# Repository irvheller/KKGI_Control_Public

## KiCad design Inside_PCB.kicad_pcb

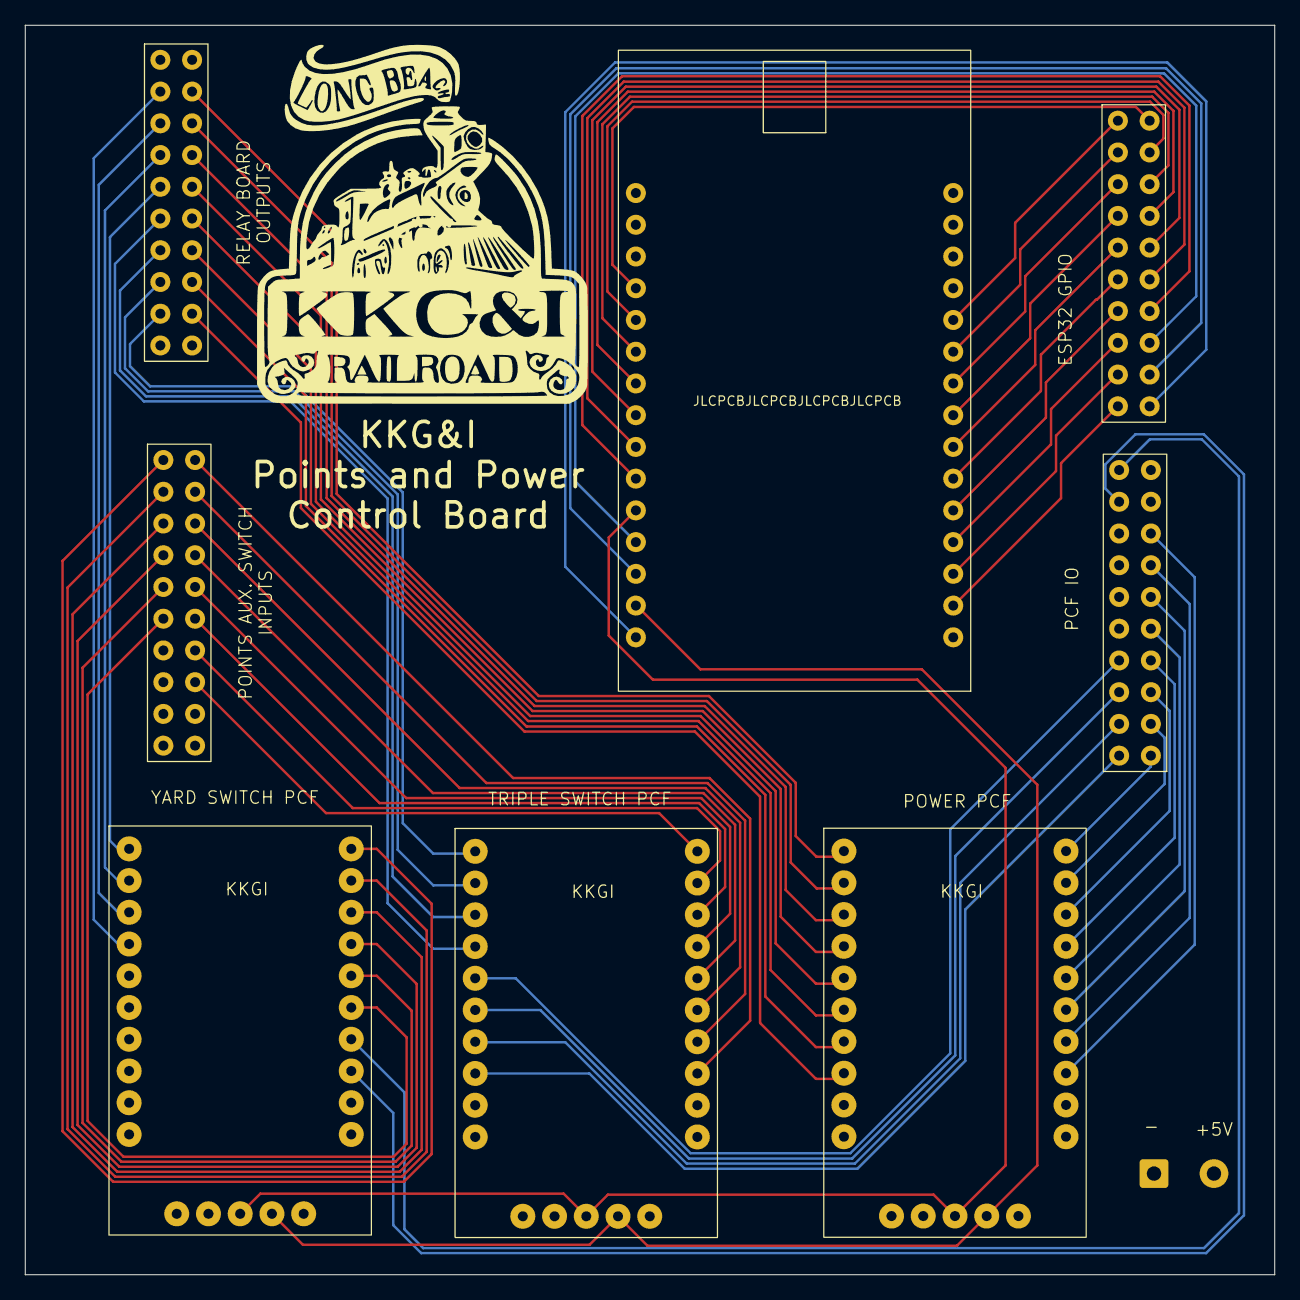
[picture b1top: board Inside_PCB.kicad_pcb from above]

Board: 4 copper layers, 100.0 x 100.0 mm, 9 parts (0 on the bottom side), 72 nets.

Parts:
J1: Screw_Terminal_01x02; SolderWire-0.5sqmm_1x02_P4.8mm_D0.9mm_OD2.3mm
U1: ESP32_DEVKIT
U2: Power PCF; PCF8575
U3: Yard Switch PCF; PCF8575
U4: Triple Switch PCF; PCF8575
U5: Points Aux Switches; 2X10_HEADER
U6: Relay Board; 2X10_HEADER
U7, U8: 2X10_HEADER

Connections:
+5V: J1.2, U1.30 (VIN), U2.2 (VD0), U2.19 (VD0), U2.22 (VCC), U3.2 (VD0), U3.19 (VD0), U3.22 (VCC), U4.2 (VD0), U4.19 (VD0), U4.22 (VCC), U6.1, U6.20
GND: J1.1, U1.2 (GND), U1.29 (GND), U2.1 (GND), U2.20 (GND), U2.21 (GND), U3.1 (GND), U3.20 (GND), U3.21 (GND), U4.1 (GND), U4.20 (GND), U4.21 (GND), U6.10, U6.11
unnamed: U1.13 (GPIO1), U8.2
unnamed: U1.4 (GPIO2), U8.10
unnamed: U1.12 (GPIO3), U8.3
unnamed: U1.5 (GPIO4), U8.9
unnamed: U1.8 (GPIO5), U8.6
unnamed: U1.26 (GPIO14), U8.11
unnamed: U1.6 (GPIO16), U8.8
unnamed: U1.7 (GPIO17), U8.7
unnamed: U1.9 (GPIO18), U8.5
unnamed: U1.10 (GPIO19), U8.4
unnamed: U1.15 (GPIO23), U8.1
unnamed: U1.23 (GPIO25), U8.14
unnamed: U1.24 (GPIO26), U8.13
unnamed: U1.25 (GPIO27), U8.12
unnamed: U1.21 (GPIO32), U8.16
unnamed: U1.22 (GPIO33), U8.15
unnamed: U1.19 (GPIO34), U8.18
unnamed: U1.20 (GPIO35), U8.17
unnamed: U1.17 (GPIO36), U8.20
unnamed: U1.18 (GPIO39), U8.19
unnamed: U1.14 (I2C_SCL), U2.24 (SCL), U3.24 (SCL), U4.24 (SCL)
unnamed: U1.11 (I2C_SDA), U2.23 (SDA), U3.23 (SDA), U4.23 (SDA)
unnamed: U2.3 (P00), U7.18
unnamed: U2.4 (P01), U7.17
unnamed: U2.5 (P02), U7.16
unnamed: U2.6 (P03), U7.15
unnamed: U2.7 (P04), U7.14
unnamed: U2.8 (P05), U7.13
unnamed: U2.9 (P06), U7.12
unnamed: U2.10 (P07), U7.11
unnamed: U2.11 (P10), U6.9
unnamed: U2.12 (P11), U6.8
unnamed: U2.13 (P12), U6.7
unnamed: U2.14 (P13), U6.6
unnamed: U2.15 (P14), U6.5
unnamed: U2.16 (P15), U6.4
unnamed: U2.17 (P16), U6.3
unnamed: U2.18 (P17), U6.2
unnamed: U3.3 (P00), U7.2
unnamed: U3.4 (P01), U7.1
unnamed: U3.5 (P02), U5.16
unnamed: U3.6 (P03), U5.15
unnamed: U3.7 (P04), U5.14
unnamed: U3.8 (P05), U5.13
unnamed: U3.9 (P06), U5.12
unnamed: U3.10 (P07), U5.11
unnamed: U3.11 (P10), U6.15
unnamed: U3.12 (P11), U6.14
unnamed: U3.13 (P12), U6.13
unnamed: U3.14 (P13), U6.12
unnamed: U3.15 (P14), U7.3
unnamed: U3.16 (P15), U7.4
unnamed: U3.17 (P16), U7.5
unnamed: U3.18 (P17), U7.6
unnamed: U4.3 (P00), U5.10
unnamed: U4.4 (P01), U5.9
unnamed: U4.5 (P02), U5.8
unnamed: U4.6 (P03), U5.7
unnamed: U4.7 (P04), U5.6
unnamed: U4.8 (P05), U5.5
unnamed: U4.9 (P06), U5.4
unnamed: U4.10 (P07), U5.3
unnamed: U4.11 (P10), U6.19
unnamed: U4.12 (P11), U6.18
unnamed: U4.13 (P12), U6.17
unnamed: U4.14 (P13), U6.16
unnamed: U4.15 (P14), U7.7
unnamed: U4.16 (P15), U7.8
unnamed: U4.17 (P16), U7.9
unnamed: U4.18 (P17), U7.10

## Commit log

2026-01-21 Clear public repo
2026-01-22 test
2026-01-24 temp
